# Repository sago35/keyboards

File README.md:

# keyboards

This repository was created to manage the circuitry and firmware for the keyboards I designed.  
The firmware is created using [sago35/tinygo-keyboard](https://github.com/sago35/tinygo-keyboard).  

## sg24

* [kicanvas](https://kicanvas.org/?github=https%3A%2F%2Fgithub.com%2Fsago35%2Fkeyboards%2Ftree%2Fmain%2Fsg24%2Fsg24)

## zero-kb02/

* [kicanvas](https://kicanvas.org/?github=https%3A%2F%2Fgithub.com%2Fsago35%2Fkeyboards%2Ftree%2Fmain%2Fzero-kb02%2Fzero-kb02)
* [gerber data for jlcpcb](./zero-kb02/zero-kb02/GERBER-zero-kb02.zip)
    * For the `Mark on PCB` item, please select `Order Number(Specify Position)`
* [case (stl / 3mf)](./zero-kb02/stl/)
* workshop - https://github.com/sago35/tinygo_keeb_workshop_2024

### pinout

| Name      | Pin            | Info
|-----------|----------------|------
| VR\_BTN   | machine.GPIO0  | InputPullup
| WS2812    | machine.GPIO1  | Output
| ROT\_BTN1 | machine.GPIO2  | InputPullup
| ROT\_A1   | machine.GPIO3  | InputPullup
| ROT\_B1   | machine.GPIO4  | InputPullup
| COL1      | machine.GPIO5  | Output
| COL2      | machine.GPIO6  | Output
| COL3      | machine.GPIO7  | Output
| COL4      | machine.GPIO8  | Output
| ROW1      | machine.GPIO9  | InputPulldown
| ROW2      | machine.GPIO10 | InputPulldown
| ROW3      | machine.GPIO11 | InputPulldown
| SDA0\_TX0 | machine.GPIO12 | I2C SDA
| SCL0\_RX0 | machine.GPIO13 | I2C SCL
| EX01      | machine.GPIO14 | GPIO
| EX02      | machine.GPIO15 | GPIO
| EX03      | machine.GPIO26 | GPIO / ADC
| EX04      | machine.GPIO27 | GPIO / ADC
| VR\_Y     | machine.GPIO28 | ADC
| VR\_X     | machine.GPIO29 | ADC

### matrix and leds

The image below represents the relationship between the COL and ROW of the MATRIX wiring, as well as the order of the LEDs.
It was created by [rdon_key](https://x.com/rdon_key).

## sg48key2

* [kicanvas](https://kicanvas.org/?github=https%3A%2F%2Fgithub.com%2Fsago35%2Fkeyboards%2Ftree%2Fmain%2Fsg48key2%2Fsg48key2)
  * Configuration of U3 is incorrect and needs to be fixed.

## conf2025badge

This is the badge for TinyGo Conference 2025 in JAPAN.

* [kicanvas](https://kicanvas.org/?github=https%3A%2F%2Fgithub.com%2Fsago35%2Fkeyboards%2Ftree%2Fmain%2Fconf2025badge%2Fconf2025badge)
* [case (stl / 3mf)](./conf2025badge/stl/)
* [build guide](./conf2025badge/build/build.md)

| No | 品名 | 個数 | 備考 |
|---|---|---|---|
| 1 | 基板 | 1 | |
| 2 | [XIAO RP2040](https://akizukidenshi.com/catalog/g/g117044/) | 1 | |
| 3 | [ジョイスティック](https://akizukidenshi.com/catalog/g/g104048/) | 1 | |
| 4 | [OLED 液晶](https://akizukidenshi.com/catalog/g/g112031/) | 1 | SSD1306 128x64 |
| 5 | [プルアップ抵抗](https://akizukidenshi.com/catalog/g/g116332/) | 2 | 3.3K (1K – 10K) |
| 6 | [キースイッチ](https://shop.yushakobo.jp/collections/all-switches) | 2 | |
| 7 | [キーキャップ](https://shop.yushakobo.jp/collections/keycaps?sort_by=created-descending&filter.v.availability=1&filter.v.price.gte=&filter.v.price.lte=) | 2 | |
| 8 | [キーソケット](https://shop.yushakobo.jp/products/a01ps?variant=37665172521121) | 2 | MX socket |
| 9 | ロータリーエンコーダー | 1 | EC11 互換、20mm Plum |
| 10 | [RGB LED](https://akizukidenshi.com/catalog/g/g115478/) | 2 | SK6812MINI-E |
| 11 | [ブザー](https://akizukidenshi.com/catalog/g/g104118/) | 1 | |
| 12 | エンコーダーノブ | 1 | |
| 13 | ハット | 1 | ジョイスティック用 |
| 14 | スイッチプレート | 1 | |
| 15 | ボトムプレート | 1 | |
| 16 | 木ねじ 2.1×10 | 2 | |

## gocon2026badge

This is the badge for Go Conference 2026.

* [kicanvas](https://kicanvas.org/?github=https%3A%2F%2Fgithub.com%2Fsago35%2Fkeyboards%2Ftree%2Fmain%2Fgocon2026badge%2Fgocon2026badge)
* [case (MakerWorld)](https://makerworld.com/ja/models/3294325-gocon2026badge-case)

| No | 品名 | 個数 | 備考 |
|---|---|---|---|
| 1 | 基板 | 1 | |
| 2 | [RP2040-Zero](https://shop.talpkeyboard.com/products/rp2040-zero-usb-c-compatible) | 1 | Waveshare |
| 3 | [TFT 液晶](https://akizukidenshi.com/catalog/g/g131019/) | 1 | ST7789 1.54 インチ 240x240 SPI |
| 4 | [RGB LED](https://akizukidenshi.com/catalog/g/g115478/) | 16 | SK6812MINI-E、5 個入りなので注意 |
| 5 | [タクトスイッチ](https://akizukidenshi.com/catalog/g/g103647/) | 5 | 6mm 角、高さ 5mm |
| 6 | Grove コネクタ | 2 | I2C / UART |

### pinout

| Name    | Pin            | Info
|---------|----------------|------
| BTN\_A  | machine.GPIO3  | InputPullup
| BTN\_B  | machine.GPIO6  | InputPullup (未搭載)
| BTN\_R  | machine.GPIO7  | InputPullup
| BTN\_U  | machine.GPIO8  | InputPullup
| WS2812  | machine.GPIO9  | Output (16 LEDs)
| LCD SCK | machine.GPIO10 | SPI1 SCK
| LCD SDO | machine.GPIO11 | SPI1 SDO
| LCD BL  | machine.GPIO12 | Output
| LCD CS  | machine.GPIO13 | Output
| LCD DC  | machine.GPIO14 | Output
| LCD RST | machine.GPIO15 | Output
| BTN\_L  | machine.GPIO28 | InputPullup
| BTN\_D  | machine.GPIO29 | InputPullup

### firmware

```
tinygo flash --target waveshare-rp2040-zero --size short --stack-size 8kb ./gocon2026badge/firmware/
```

| Button on badge screen | Screen |
|---|---|
| A | Timetable |
| U | Breakout |
| R | Cyclone game |
| D | 3D demo |
| L | Name tag (D shows the QR code) |

Press A on each screen to go back to the badge screen.

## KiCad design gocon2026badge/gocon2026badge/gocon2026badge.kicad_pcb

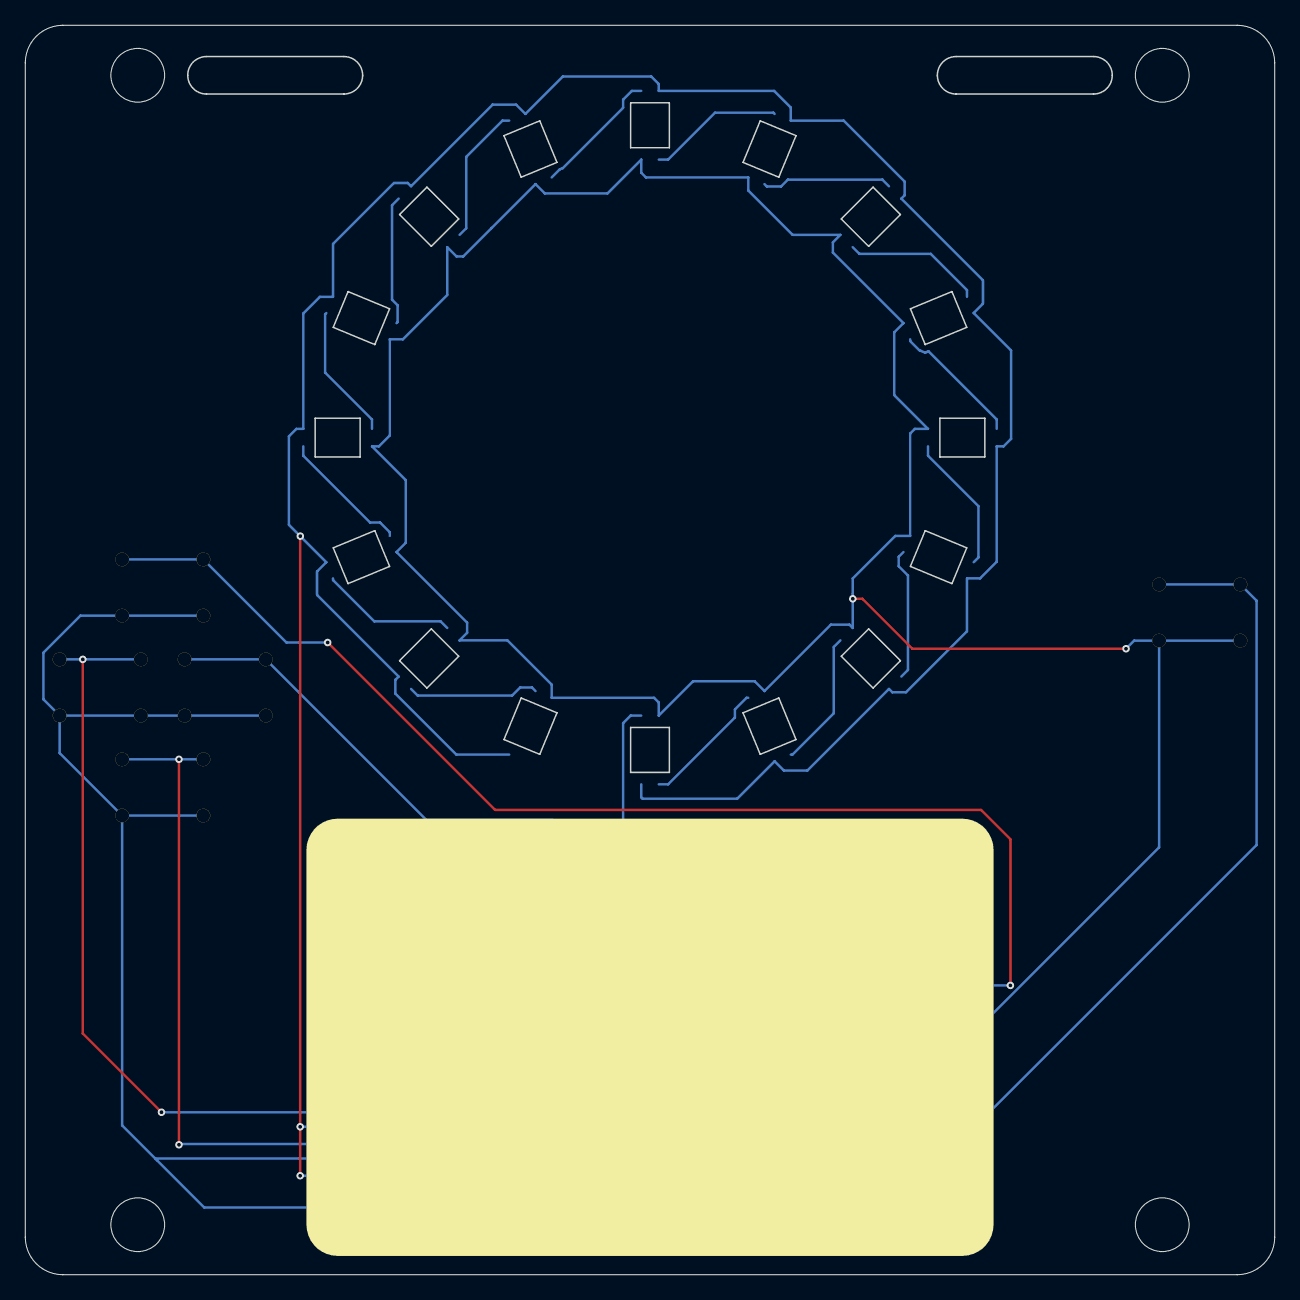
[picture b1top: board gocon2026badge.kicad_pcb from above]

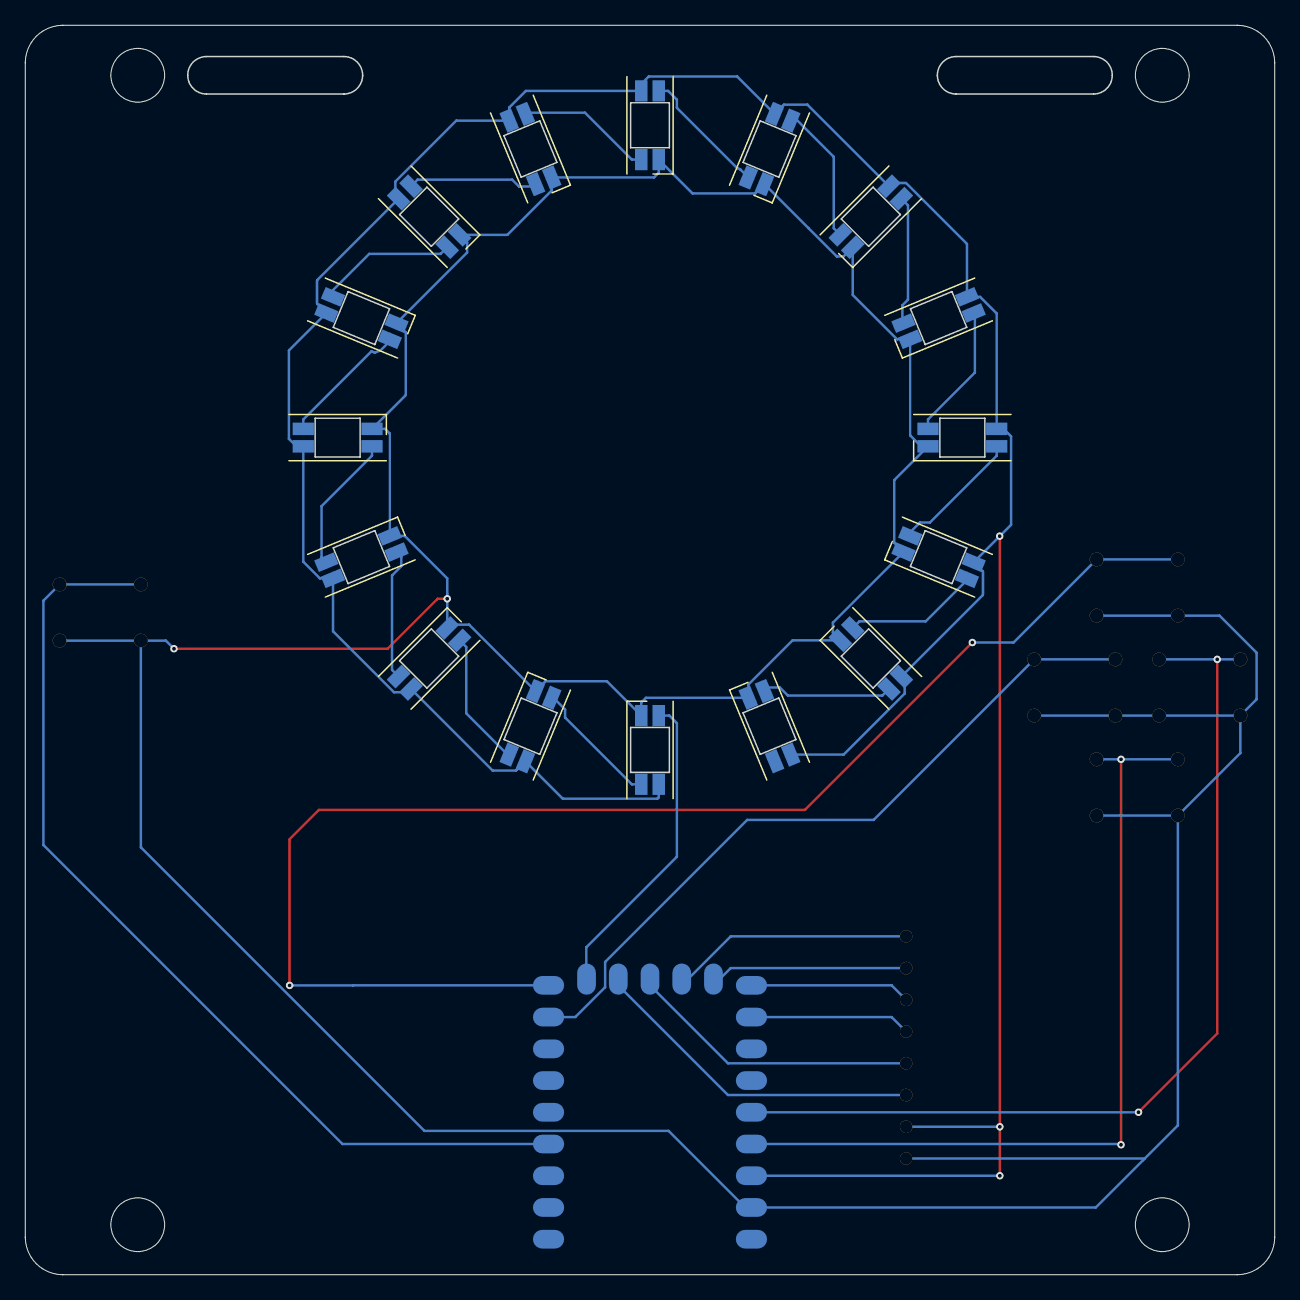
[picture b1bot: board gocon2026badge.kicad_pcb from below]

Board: 2 copper layers, 100.0 x 100.0 mm, 29 parts (17 on the bottom side), 29 nets.

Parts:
LED1, LED2, LED3, LED4, LED5, LED6, LED7, LED8, LED9, LED10, LED11, LED12, LED13, LED14, LED15, LED16: YS-SK6812MINI-E
SW1, SW2, SW3, SW4, SW5: SW_PUSH; SW_PUSH_6mm_H5mm-b
U1: rp2040-zero; rp2040-zero-smd
U2: ST7789-1.54TFT-SPI; ST7789-1.54TFT-SPI-b
U91, U92, U93, U94: (no value)
hole1, hole2: strap_hole

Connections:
BL: U1.13 (12), U2.8 (BL)
BTN_A: SW5.1, U1.4 (3)
BTN_DOWN: SW3.1, U1.20 (29)
BTN_LEFT: SW2.1, U1.19 (28)
BTN_RIGHT: SW4.1, U1.8 (7)
BTN_UP: SW1.1, U1.9 (8)
CS: U1.14 (13), U2.7 (CS)
DC: U1.15 (14), U2.6 (DC)
GND: LED1.3 (VSS), LED2.3 (VSS), LED3.3 (VSS), LED4.3 (VSS), LED5.3 (VSS), LED6.3 (VSS), LED7.3 (VSS), LED8.3 (VSS), LED9.3 (VSS), LED10.3 (VSS), LED11.3 (VSS), LED12.3 (VSS), LED13.3 (VSS), LED14.3 (VSS), LED15.3 (VSS), LED16.3 (VSS), SW1.2, SW2.2, SW3.2, SW4.2, SW5.2, U1.22 (GND), U2.1 (GND)
unnamed: LED1.2 (DOUT), LED2.4 (DIN)
unnamed: LED2.2 (DOUT), LED3.4 (DIN)
unnamed: LED3.2 (DOUT), LED4.4 (DIN)
unnamed: LED4.2 (DOUT), LED5.4 (DIN)
unnamed: LED5.2 (DOUT), LED6.4 (DIN)
unnamed: LED6.2 (DOUT), LED7.4 (DIN)
unnamed: LED7.2 (DOUT), LED8.4 (DIN)
unnamed: LED8.2 (DOUT), LED9.4 (DIN)
unnamed: LED9.2 (DOUT), LED10.4 (DIN)
unnamed: LED10.2 (DOUT), LED11.4 (DIN)
unnamed: LED11.2 (DOUT), LED12.4 (DIN)
unnamed: LED12.2 (DOUT), LED13.4 (DIN)
unnamed: LED13.2 (DOUT), LED14.4 (DIN)
unnamed: LED14.2 (DOUT), LED15.4 (DIN)
unnamed: LED15.2 (DOUT), LED16.4 (DIN)
RST: U1.16 (15), U2.5 (RST)
SPI_SCK: U1.11 (10), U2.3 (SCL)
SPI_SDO: U1.12 (11), U2.4 (SDA)
VCC: LED1.1 (VDD), LED2.1 (VDD), LED3.1 (VDD), LED4.1 (VDD), LED5.1 (VDD), LED6.1 (VDD), LED7.1 (VDD), LED8.1 (VDD), LED9.1 (VDD), LED10.1 (VDD), LED11.1 (VDD), LED12.1 (VDD), LED13.1 (VDD), LED14.1 (VDD), LED15.1 (VDD), LED16.1 (VDD), U1.21 (3V3), U2.2 (VCC)
WS2812B: LED1.4 (DIN), U1.10 (9)

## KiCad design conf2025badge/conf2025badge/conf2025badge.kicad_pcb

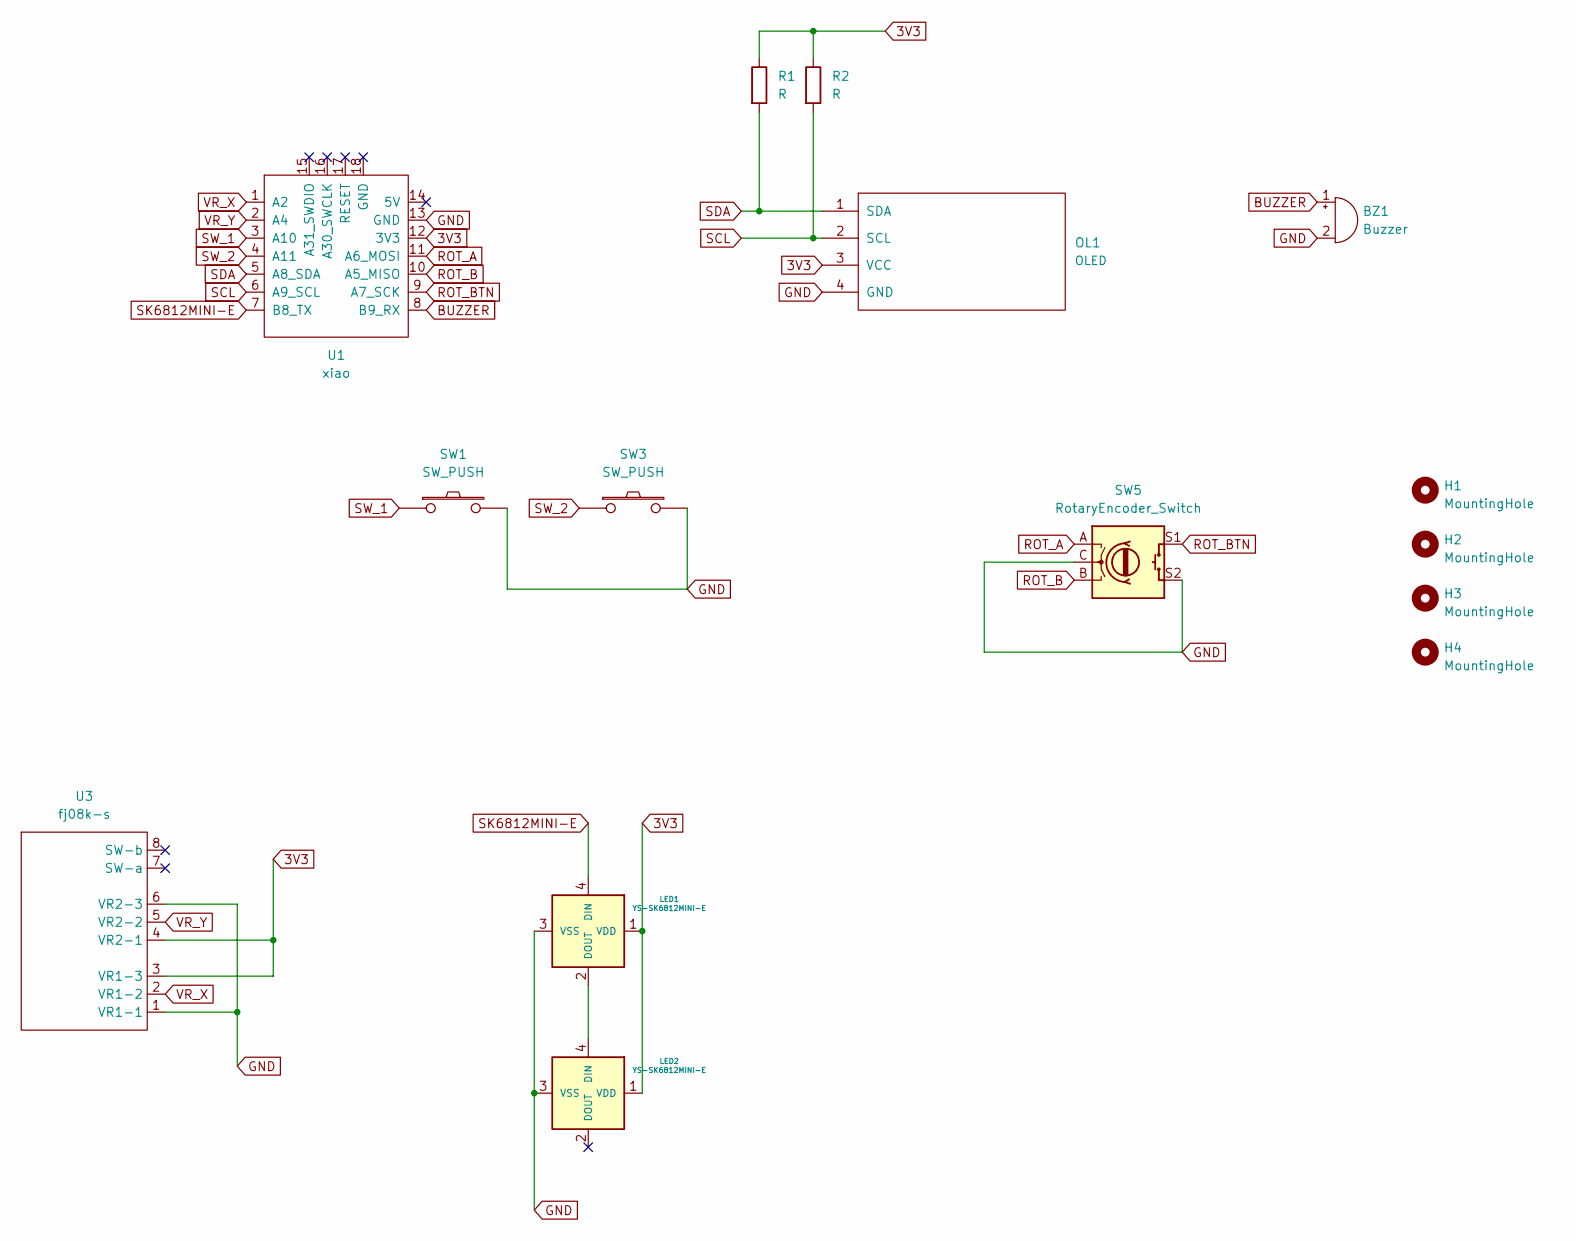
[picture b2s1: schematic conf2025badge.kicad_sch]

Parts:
BZ1: Buzzer; buzzer 5.5mm
H1, H2, H3, H4: MountingHole; M2_HOLE_v2
LED1, LED2: YS-SK6812MINI-E
OL1: OLED
R1, R2: R; R_Axial_DIN0207_L6.3mm_D2.5mm_P10.16mm_Horizontal
SW1, SW3: SW_PUSH; CherryMX_Hotswap
SW5: RotaryEncoder_Switch; RotaryEncoder_Alps_EC11E-Switch_Vertical_H20mm
U1: xiao; xiao-tht
U3: fj08k-s; FJ08K-S

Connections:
3V3: LED1.1 (VDD), LED2.1 (VDD), OL1.3 (VCC), R1.1, R2.1, U1.12 (3V3), U3.3 (VR1-3), U3.4 (VR2-1)
BUZZER: BZ1.1 (+), U1.8 (B9_RX)
GND: BZ1.2 (-), LED1.3 (VSS), LED2.3 (VSS), OL1.4 (GND), SW1.2, SW3.2, SW5.C, SW5.S2, U1.13 (GND), U3.1 (VR1-1), U3.6 (VR2-3)
unnamed: LED1.2 (DOUT), LED2.4 (DIN)
ROT_A: SW5.A, U1.11 (A6_MOSI)
ROT_B: SW5.B, U1.10 (A5_MISO)
ROT_BTN: SW5.S1, U1.9 (A7_SCK)
SCL: OL1.2 (SCL), R2.2, U1.6 (A9_SCL)
SDA: OL1.1 (SDA), R1.2, U1.5 (A8_SDA)
SK6812MINI-E: LED1.4 (DIN), U1.7 (B8_TX)
SW_1: SW1.1, U1.3 (A10)
SW_2: SW3.1, U1.4 (A11)
VR_X: U1.1 (A2), U3.2 (VR1-2)
VR_Y: U1.2 (A4), U3.5 (VR2-2)

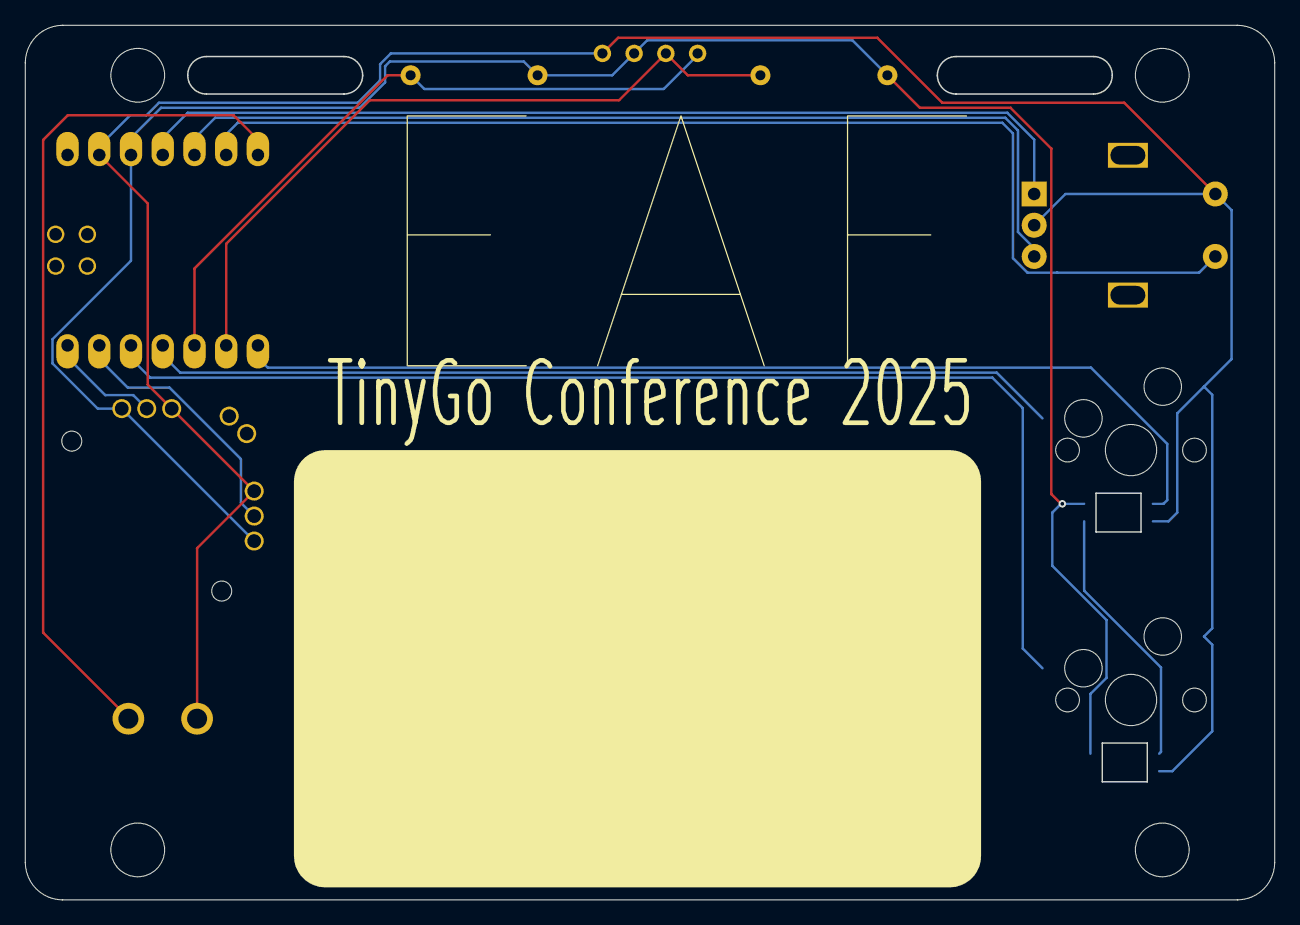
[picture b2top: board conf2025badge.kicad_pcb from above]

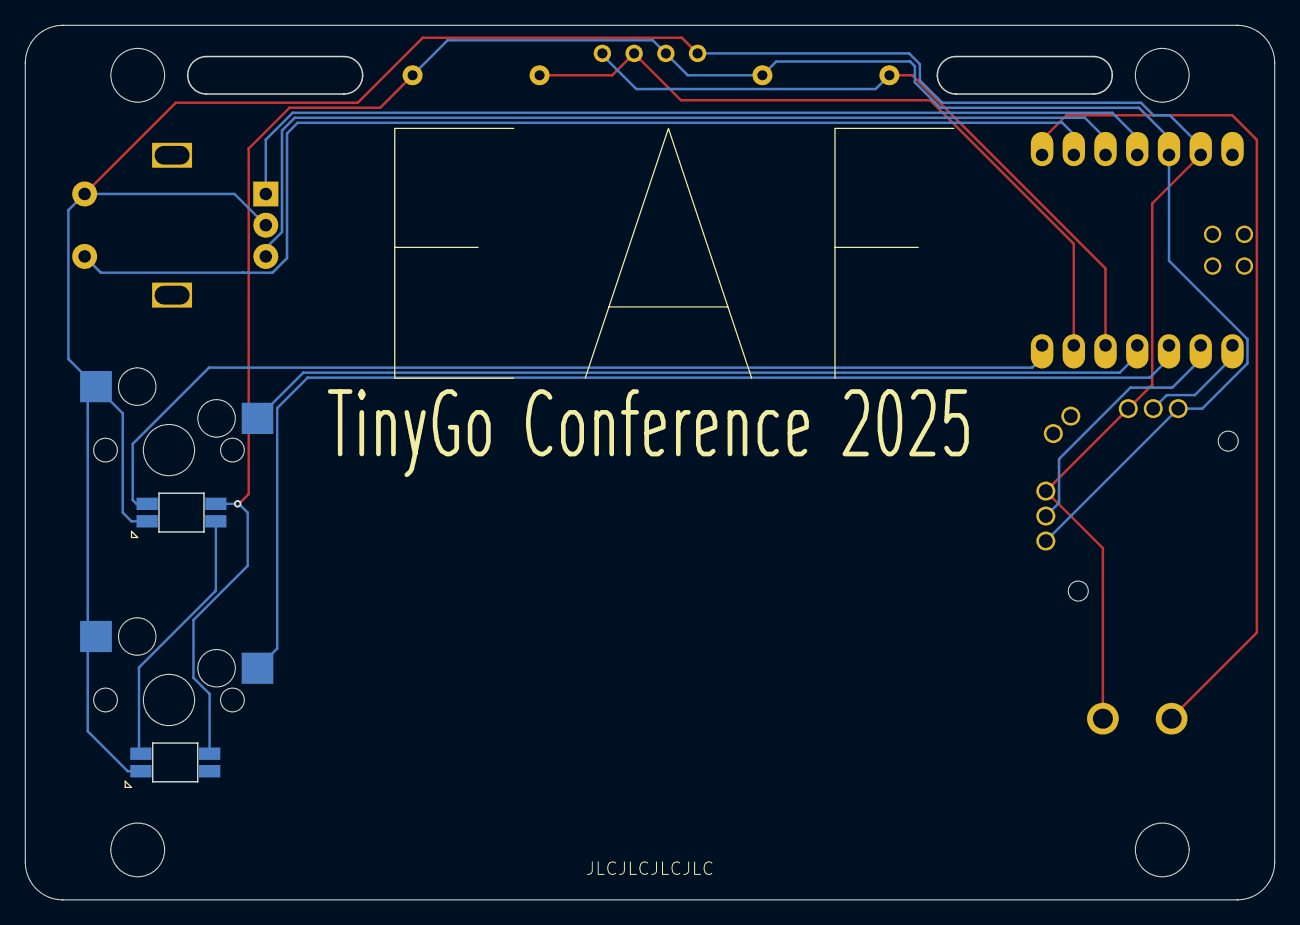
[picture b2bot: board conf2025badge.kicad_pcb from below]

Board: 2 copper layers, 100.0 x 70.0 mm, 17 parts (2 on the bottom side), 14 nets.

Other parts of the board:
SW2, SW2#2: KEY_SWITCH; strap_hole

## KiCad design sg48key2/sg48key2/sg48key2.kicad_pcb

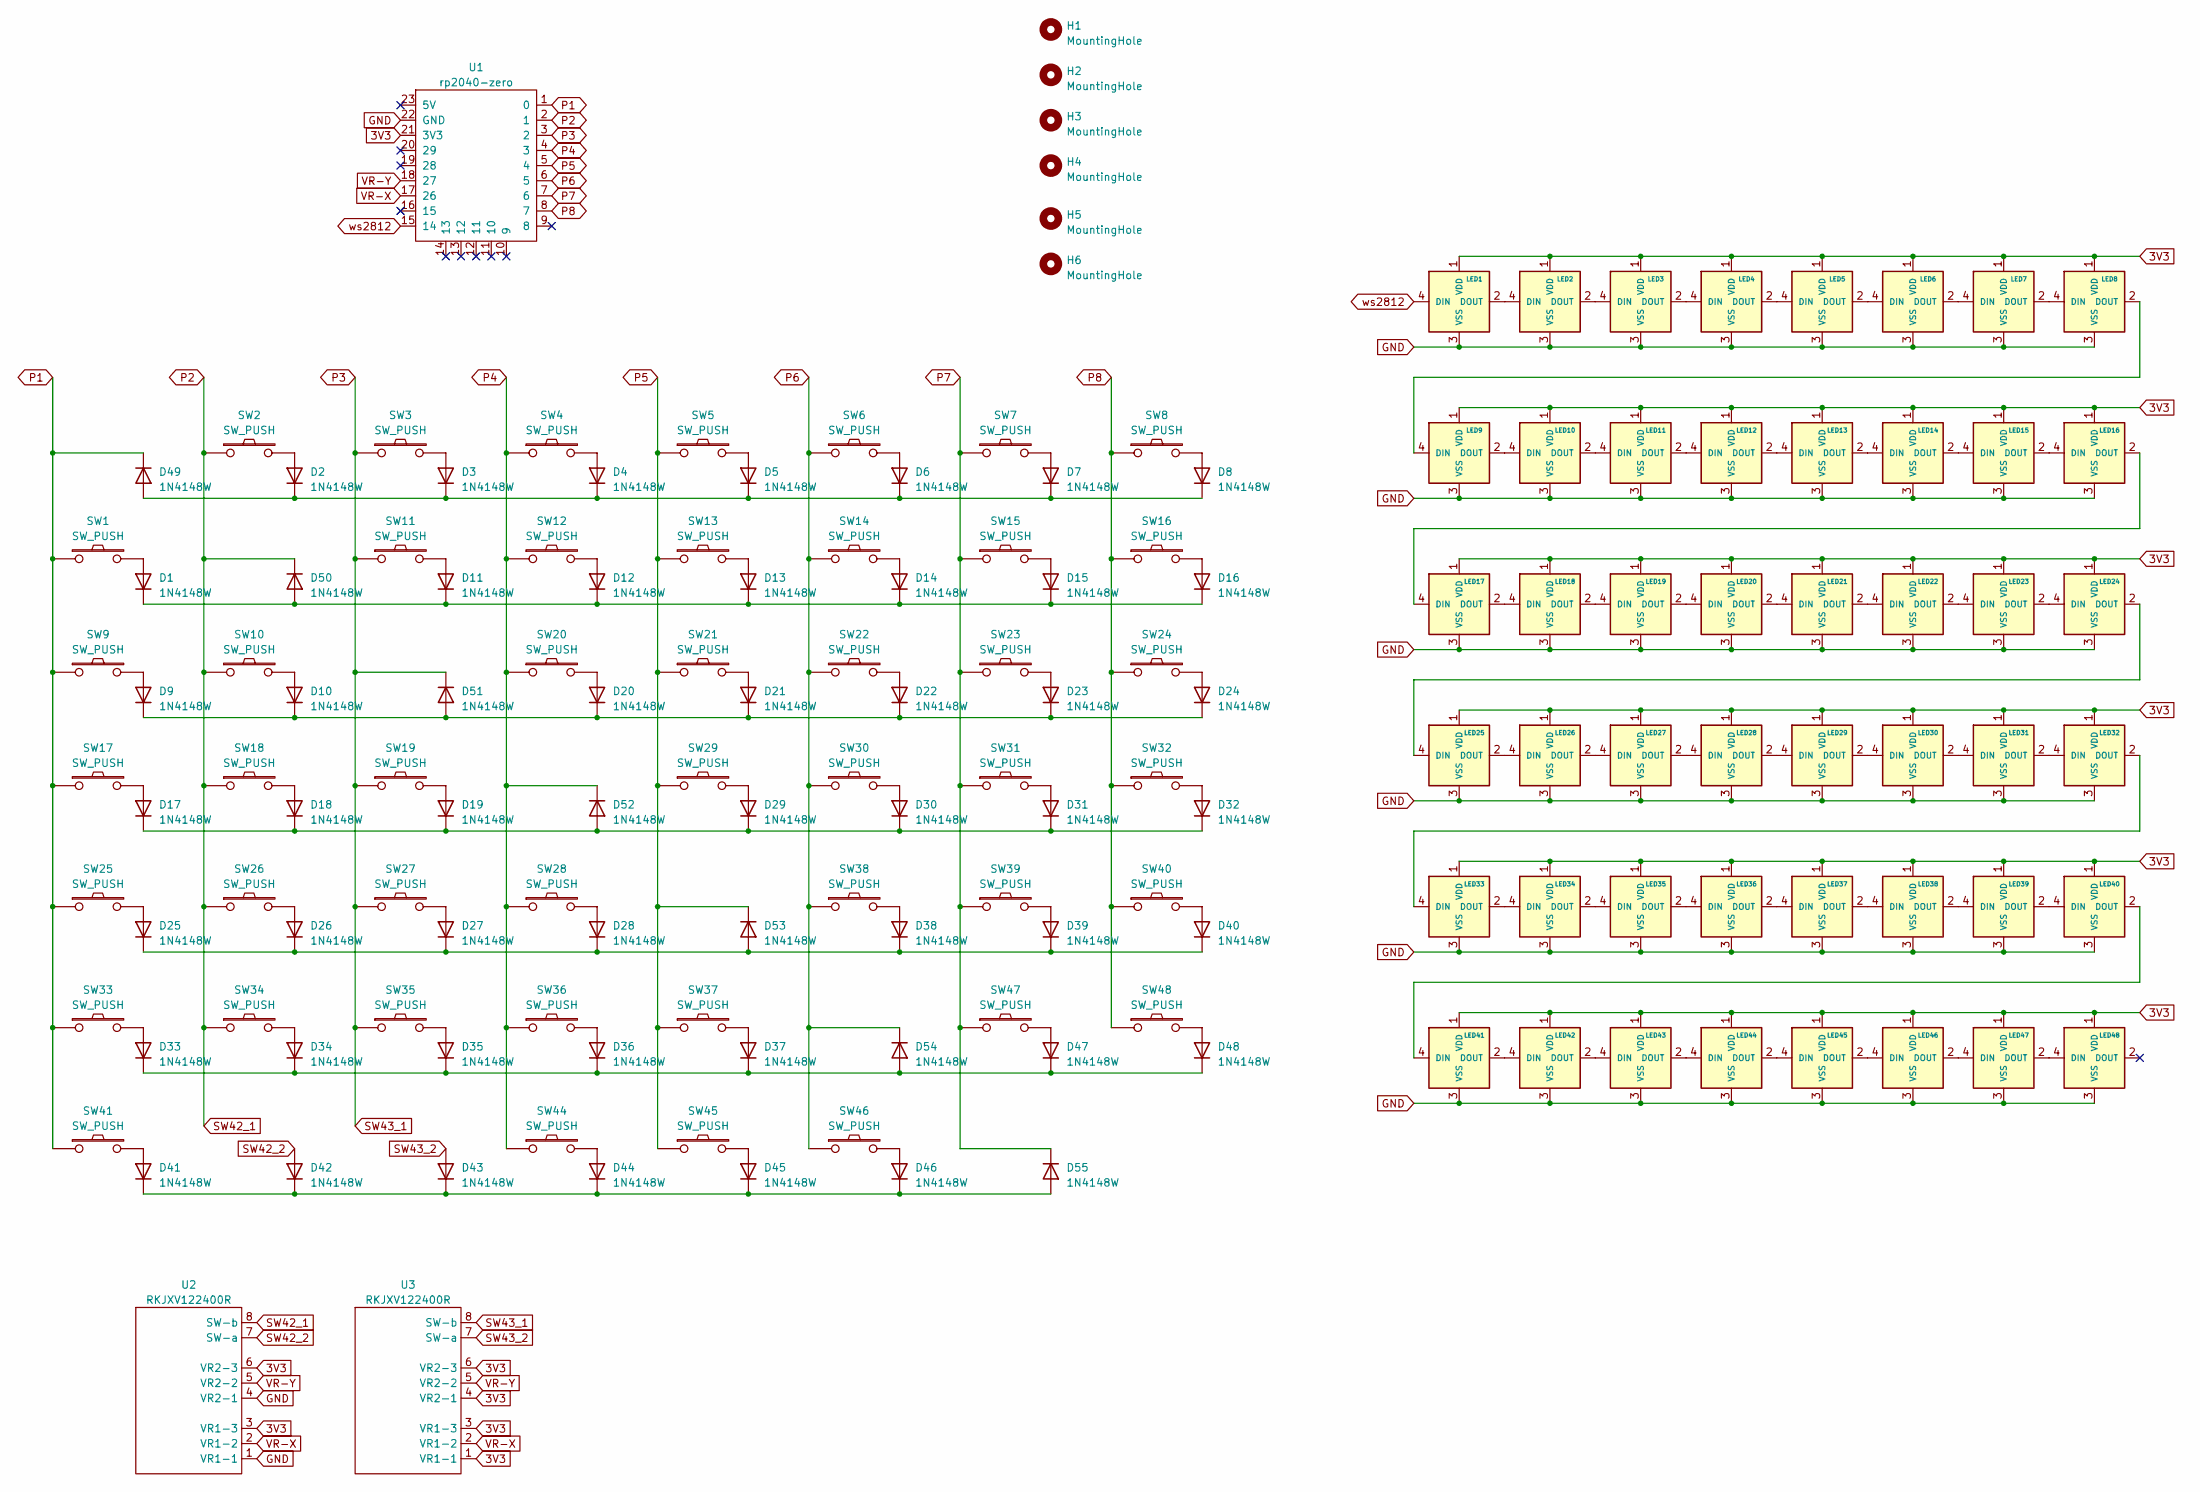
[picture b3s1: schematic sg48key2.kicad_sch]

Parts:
D1, D2, D3, D4, D5, D6, D7, D8, D9, D10, D11, D12, D13, D14, D15, D16, D17, D18, D19, D20, D21, D22, D23, D24, D25, D26, D27, D28, D29, D30, D31, D32, D33, D34, D35, D36, D37, D38, D39, D40, D41, D42, D43, D44, D45, D46, D47, D48, D49, D50, D51, D52, D53, D54, D55: 1N4148W; D3_SMD_v2
H1, H2, H3, H4, H5, H6: MountingHole; Hole-2.5mm
LED1, LED2, LED3, LED4, LED5, LED6, LED7, LED8, LED9, LED10, LED11, LED12, LED13, LED14, LED15, LED16, LED17, LED18, LED19, LED20, LED21, LED22, LED23, LED24, LED25, LED26, LED27, LED28, LED29, LED30, LED31, LED32, LED33, LED34, LED35, LED36, LED37, LED38, LED39, LED40, LED41, LED42, LED43, LED44, LED45, LED46, LED47, LED48: YS-SK6812MINI-E
SW1, SW2, SW3, SW4, SW5, SW6, SW7, SW8, SW9, SW10, SW11, SW12, SW13, SW14, SW15, SW16, SW17, SW18, SW19, SW20, SW21, SW22, SW23, SW24, SW25, SW26, SW27, SW28, SW29, SW30, SW31, SW32, SW33, SW34, SW35, SW36, SW37, SW38, SW39, SW40, SW41, SW44, SW45, SW46, SW47, SW48: SW_PUSH; ChocV1_V2_Hotswap
U1: rp2040-zero; rp2040-zero_wide_with_choc_socket
U2, U3: RKJXV122400R; FJ08K-S_ChocV1_V2_Hotswap

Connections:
3V3: LED1.1 (VDD), LED2.1 (VDD), LED3.1 (VDD), LED4.1 (VDD), LED5.1 (VDD), LED6.1 (VDD), LED7.1 (VDD), LED8.1 (VDD), LED9.1 (VDD), LED10.1 (VDD), LED11.1 (VDD), LED12.1 (VDD), LED13.1 (VDD), LED14.1 (VDD), LED15.1 (VDD), LED16.1 (VDD), LED17.1 (VDD), LED18.1 (VDD), LED19.1 (VDD), LED20.1 (VDD), LED21.1 (VDD), LED22.1 (VDD), LED23.1 (VDD), LED24.1 (VDD), LED25.1 (VDD), LED26.1 (VDD), LED27.1 (VDD), LED28.1 (VDD), LED29.1 (VDD), LED30.1 (VDD), LED31.1 (VDD), LED32.1 (VDD), LED33.1 (VDD), LED34.1 (VDD), LED35.1 (VDD), LED36.1 (VDD), LED37.1 (VDD), LED38.1 (VDD), LED39.1 (VDD), LED40.1 (VDD), LED41.1 (VDD), LED42.1 (VDD), LED43.1 (VDD), LED44.1 (VDD), LED45.1 (VDD), LED46.1 (VDD), LED47.1 (VDD), LED48.1 (VDD), U1.21 (3V3), U2.3 (VR1-3), U2.6 (VR2-3), U3.1 (VR1-1), U3.3 (VR1-3), U3.4 (VR2-1), U3.6 (VR2-3)
GND: LED1.3 (VSS), LED2.3 (VSS), LED3.3 (VSS), LED4.3 (VSS), LED5.3 (VSS), LED6.3 (VSS), LED7.3 (VSS), LED8.3 (VSS), LED9.3 (VSS), LED10.3 (VSS), LED11.3 (VSS), LED12.3 (VSS), LED13.3 (VSS), LED14.3 (VSS), LED15.3 (VSS), LED16.3 (VSS), LED17.3 (VSS), LED18.3 (VSS), LED19.3 (VSS), LED20.3 (VSS), LED21.3 (VSS), LED22.3 (VSS), LED23.3 (VSS), LED24.3 (VSS), LED25.3 (VSS), LED26.3 (VSS), LED27.3 (VSS), LED28.3 (VSS), LED29.3 (VSS), LED30.3 (VSS), LED31.3 (VSS), LED32.3 (VSS), LED33.3 (VSS), LED34.3 (VSS), LED35.3 (VSS), LED36.3 (VSS), LED37.3 (VSS), LED38.3 (VSS), LED39.3 (VSS), LED40.3 (VSS), LED41.3 (VSS), LED42.3 (VSS), LED43.3 (VSS), LED44.3 (VSS), LED45.3 (VSS), LED46.3 (VSS), LED47.3 (VSS), LED48.3 (VSS), U1.22 (GND), U2.1 (VR1-1), U2.4 (VR2-1)
unnamed: D1.2 (A), SW1.2
unnamed: D1.1 (K), D11.1 (K), D12.1 (K), D13.1 (K), D14.1 (K), D15.1 (K), D16.1 (K), D50.2 (A)
unnamed: D2.2 (A), SW2.2
unnamed: D2.1 (K), D3.1 (K), D4.1 (K), D5.1 (K), D6.1 (K), D7.1 (K), D8.1 (K), D49.2 (A)
unnamed: D3.2 (A), SW3.2
unnamed: D4.2 (A), SW4.2
unnamed: D5.2 (A), SW5.2
unnamed: D6.2 (A), SW6.2
unnamed: D7.2 (A), SW7.2
unnamed: D8.2 (A), SW8.2
unnamed: D9.2 (A), SW9.2
unnamed: D10.2 (A), SW10.2
unnamed: D9.1 (K), D10.1 (K), D20.1 (K), D21.1 (K), D22.1 (K), D23.1 (K), D24.1 (K), D51.2 (A)
unnamed: D11.2 (A), SW11.2
unnamed: D12.2 (A), SW12.2
unnamed: D13.2 (A), SW13.2
unnamed: D14.2 (A), SW14.2
unnamed: D15.2 (A), SW15.2
unnamed: D16.2 (A), SW16.2
unnamed: D17.2 (A), SW17.2
unnamed: D17.1 (K), D18.1 (K), D19.1 (K), D29.1 (K), D30.1 (K), D31.1 (K), D32.1 (K), D52.2 (A)
unnamed: D18.2 (A), SW18.2
unnamed: D19.2 (A), SW19.2
unnamed: D20.2 (A), SW20.2
unnamed: D21.2 (A), SW21.2
unnamed: D22.2 (A), SW22.2
unnamed: D23.2 (A), SW23.2
unnamed: D24.2 (A), SW24.2
unnamed: D25.2 (A), SW25.2
unnamed: D25.1 (K), D26.1 (K), D27.1 (K), D28.1 (K), D38.1 (K), D39.1 (K), D40.1 (K), D53.2 (A)
unnamed: D26.2 (A), SW26.2
unnamed: D27.2 (A), SW27.2
unnamed: D28.2 (A), SW28.2
unnamed: D29.2 (A), SW29.2
unnamed: D30.2 (A), SW30.2
unnamed: D31.2 (A), SW31.2
unnamed: D32.2 (A), SW32.2
unnamed: D33.2 (A), SW33.2
unnamed: D33.1 (K), D34.1 (K), D35.1 (K), D36.1 (K), D37.1 (K), D47.1 (K), D48.1 (K), D54.2 (A)
unnamed: D34.2 (A), SW34.2
unnamed: D35.2 (A), SW35.2
unnamed: D36.2 (A), SW36.2
unnamed: D37.2 (A), SW37.2
unnamed: D38.2 (A), SW38.2
unnamed: D39.2 (A), SW39.2
unnamed: D40.2 (A), SW40.2
unnamed: D41.2 (A), SW41.2
unnamed: D41.1 (K), D42.1 (K), D43.1 (K), D44.1 (K), D45.1 (K), D46.1 (K), D55.2 (A)
unnamed: D44.2 (A), SW44.2
unnamed: D45.2 (A), SW45.2
unnamed: D46.2 (A), SW46.2
unnamed: D47.2 (A), SW47.2
unnamed: D48.2 (A), SW48.2
unnamed: LED1.2 (DOUT), LED2.4 (DIN)
unnamed: LED2.2 (DOUT), LED3.4 (DIN)
unnamed: LED3.2 (DOUT), LED4.4 (DIN)
unnamed: LED4.2 (DOUT), LED5.4 (DIN)
unnamed: LED5.2 (DOUT), LED6.4 (DIN)
unnamed: LED6.2 (DOUT), LED7.4 (DIN)
unnamed: LED7.2 (DOUT), LED8.4 (DIN)
unnamed: LED8.2 (DOUT), LED9.4 (DIN)
unnamed: LED9.2 (DOUT), LED10.4 (DIN)
unnamed: LED10.2 (DOUT), LED11.4 (DIN)
unnamed: LED11.2 (DOUT), LED12.4 (DIN)
unnamed: LED12.2 (DOUT), LED13.4 (DIN)
unnamed: LED13.2 (DOUT), LED14.4 (DIN)
unnamed: LED14.2 (DOUT), LED15.4 (DIN)
unnamed: LED15.2 (DOUT), LED16.4 (DIN)
unnamed: LED16.2 (DOUT), LED17.4 (DIN)
unnamed: LED17.2 (DOUT), LED18.4 (DIN)
unnamed: LED18.2 (DOUT), LED19.4 (DIN)
unnamed: LED19.2 (DOUT), LED20.4 (DIN)
unnamed: LED20.2 (DOUT), LED21.4 (DIN)
unnamed: LED21.2 (DOUT), LED22.4 (DIN)
unnamed: LED22.2 (DOUT), LED23.4 (DIN)
unnamed: LED23.2 (DOUT), LED24.4 (DIN)
unnamed: LED24.2 (DOUT), LED25.4 (DIN)
unnamed: LED25.2 (DOUT), LED26.4 (DIN)
unnamed: LED26.2 (DOUT), LED27.4 (DIN)
unnamed: LED27.2 (DOUT), LED28.4 (DIN)
unnamed: LED28.2 (DOUT), LED29.4 (DIN)
unnamed: LED29.2 (DOUT), LED30.4 (DIN)
unnamed: LED30.2 (DOUT), LED31.4 (DIN)
unnamed: LED31.2 (DOUT), LED32.4 (DIN)
unnamed: LED32.2 (DOUT), LED33.4 (DIN)
unnamed: LED33.2 (DOUT), LED34.4 (DIN)
unnamed: LED34.2 (DOUT), LED35.4 (DIN)
unnamed: LED35.2 (DOUT), LED36.4 (DIN)
unnamed: LED36.2 (DOUT), LED37.4 (DIN)
unnamed: LED37.2 (DOUT), LED38.4 (DIN)
unnamed: LED38.2 (DOUT), LED39.4 (DIN)
unnamed: LED39.2 (DOUT), LED40.4 (DIN)
unnamed: LED40.2 (DOUT), LED41.4 (DIN)
unnamed: LED41.2 (DOUT), LED42.4 (DIN)
unnamed: LED42.2 (DOUT), LED43.4 (DIN)
unnamed: LED43.2 (DOUT), LED44.4 (DIN)
unnamed: LED44.2 (DOUT), LED45.4 (DIN)
unnamed: LED45.2 (DOUT), LED46.4 (DIN)
unnamed: LED46.2 (DOUT), LED47.4 (DIN)
unnamed: LED47.2 (DOUT), LED48.4 (DIN)
P1: D49.1 (K), SW1.1, SW9.1, SW17.1, SW25.1, SW33.1, SW41.1, U1.1 (0)
P2: D50.1 (K), SW2.1, SW10.1, SW18.1, SW26.1, SW34.1, U1.2 (1), U2.8 (SW-b)
P3: D51.1 (K), SW3.1, SW11.1, SW19.1, SW27.1, SW35.1, U1.3 (2), U3.8 (SW-b)
P4: D52.1 (K), SW4.1, SW12.1, SW20.1, SW28.1, SW36.1, SW44.1, U1.4 (3)
P5: D53.1 (K), SW5.1, SW13.1, SW21.1, SW29.1, SW37.1, SW45.1, U1.5 (4)
P6: D54.1 (K), SW6.1, SW14.1, SW22.1, SW30.1, SW38.1, SW46.1, U1.6 (5)
P7: D55.1 (K), SW7.1, SW15.1, SW23.1, SW31.1, SW39.1, SW47.1, U1.7 (6)
P8: SW8.1, SW16.1, SW24.1, SW32.1, SW40.1, SW48.1, U1.8 (7)
SW42_2: D42.2 (A), U2.7 (SW-a)
SW43_2: D43.2 (A), U3.7 (SW-a)
VR-X: U1.17 (26), U2.2 (VR1-2), U3.2 (VR1-2)
VR-Y: U1.18 (27), U2.5 (VR2-2), U3.5 (VR2-2)
ws2812: LED1.4 (DIN), U1.15 (14)

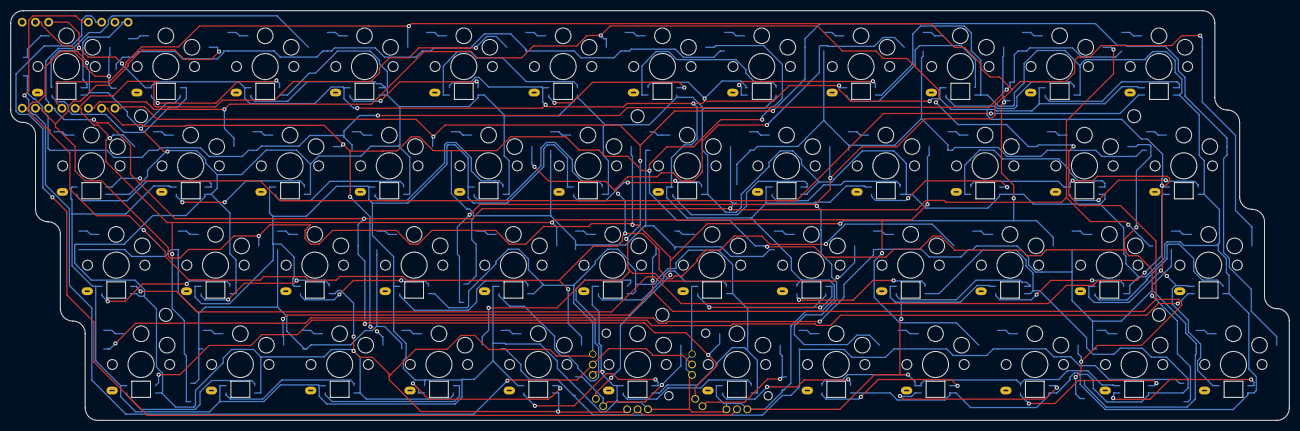
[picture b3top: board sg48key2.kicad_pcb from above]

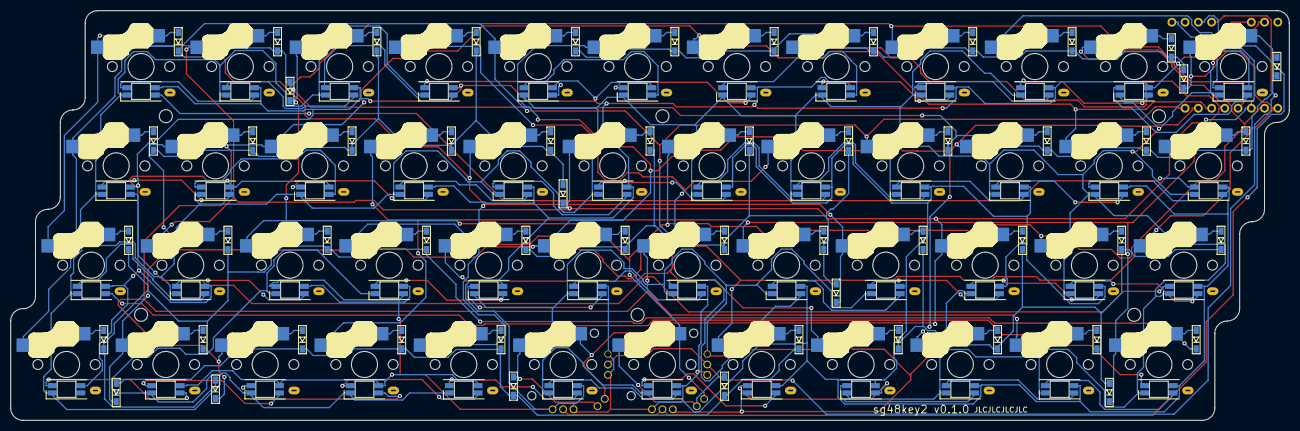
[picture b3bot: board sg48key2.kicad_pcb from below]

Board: 2 copper layers, 245.3 x 78.6 mm, 158 parts (104 on the bottom side), 115 nets.

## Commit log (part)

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2024-03-12 Add github.com/foostan/kbd
2024-03-12 Add github.com/crides/kleeb
2024-03-12 Add lib/sglib
2024-03-12 Add sg24
2024-03-12 Add .gitignore
2024-03-12 Add README.md
2024-03-14 Add LICENSE.txt
2024-03-24 Add sg24/firmware
2024-06-16 Add zero-kb02
2024-06-16 Add some parts to ./lib
2024-06-24 go mod
2024-06-24 Add Makefile
2024-06-24 Add zero-kb02/firmware
2024-06-29 Fix missing call to d.Init()
2024-07-18 Fix settings of vial.json
2024-07-18 Add invertRotaryPins to zero-kb02/firmware
2024-07-18 Add a setting to invert the pins of the rotary encoder
2024-07-18 Add ci.yml for GitHub Actions
2024-07-31 Update pio/piolib
2024-07-31 Add LED lighting functionality
2024-07-31 Change default setting of zero-kb02
2024-08-02 Update setting for zero-kb02
2024-08-04 Add images
2024-08-09 Workaround: Replace time.Tick() with time.Sleep() to address the issue of I2C freezing
2024-08-11 Add pinout
2024-08-27 Add zero-kb02/stl
2024-08-27 Add zero-kb02/stl/*.3mf
2024-09-02 Fix pinout
2024-09-02 Change I2C frequency of zero-kb02
2024-09-23 Add ./panel25
2024-09-30 Remove
2024-09-30 Add ./panel25/firmware/
2024-09-30 Add ./panel25/firmware/ (#3)
2024-10-03 Add support for panel25's RGB LEDs
2024-11-07 display shortly the layer when is changed
2024-11-07 display shortly the layer when is changed (#4)
2024-11-08 zero-kb02: change to go back to the original display after showing the layer
2024-11-19 Update go.sum (#5)
2024-11-27 Update README.md
    Fix pin assignment for EX2-4.
2024-12-01 Update README.md (#6)
    Fix pin assignment for EX2-4.
2024-12-03 Implement switching to koebiten
2024-12-03 Update Makefile
2024-12-04 Fix rotary encoder
2024-12-04 Implement switching to koebiten (#7)
2024-12-12 Update ./zero-kb02/stl/ to v44
2024-12-22 Change transition to Koebiten to occur when `To(5)` is released
2025-01-04 Update ./lib
2025-01-04 Add ./sg48key2/
2025-01-07 Add images/zero-kb02-matrix-and-led.png
2025-01-11 Change import path
2025-01-11 Add ./sg48key2/firmware/
2025-06-03 Add gerber data for JLCPCB
2025-06-03 Add gerber data for JLCPCB (#11)
2025-06-12 Update zero-kb02/stl
2025-08-12 Update lib
2025-08-12 Add ./conf2025badge
2025-09-01 Adapt to *ssd1306.Device change
2025-09-07 Update ./panel25/firmware
2025-09-18 go mod : incorporated changes to endpoints configuration
2025-09-18 go mod : incorporated changes to endpoints configuration (#14)
2025-10-04 Add ./conf2025badge/firmware
2025-10-04 Copy from https://github.com/akinobufujii/lifegame_tinygo/blob/master/lifegame.go
2025-10-04 Add ./conf2025badge/stl and ./images/conf2025badge.jpg
2025-10-04 Add ./conf2025badge/stl/conf2025badge.stl
2025-10-05 Make LEDs light up when a key is pressed
2025-10-05 Update ./conf2025badge/stl/
2025-10-06 Enable sound to ./conf2025badge
2025-10-07 Add build guide for conf2025badge
2025-10-08 Fix led
2025-10-09 Update conf2025badge PCB (move buzzer down)
2026-02-12 Add wsLed support
2026-02-12 Change key settings
2026-02-13 Add invert_diode
